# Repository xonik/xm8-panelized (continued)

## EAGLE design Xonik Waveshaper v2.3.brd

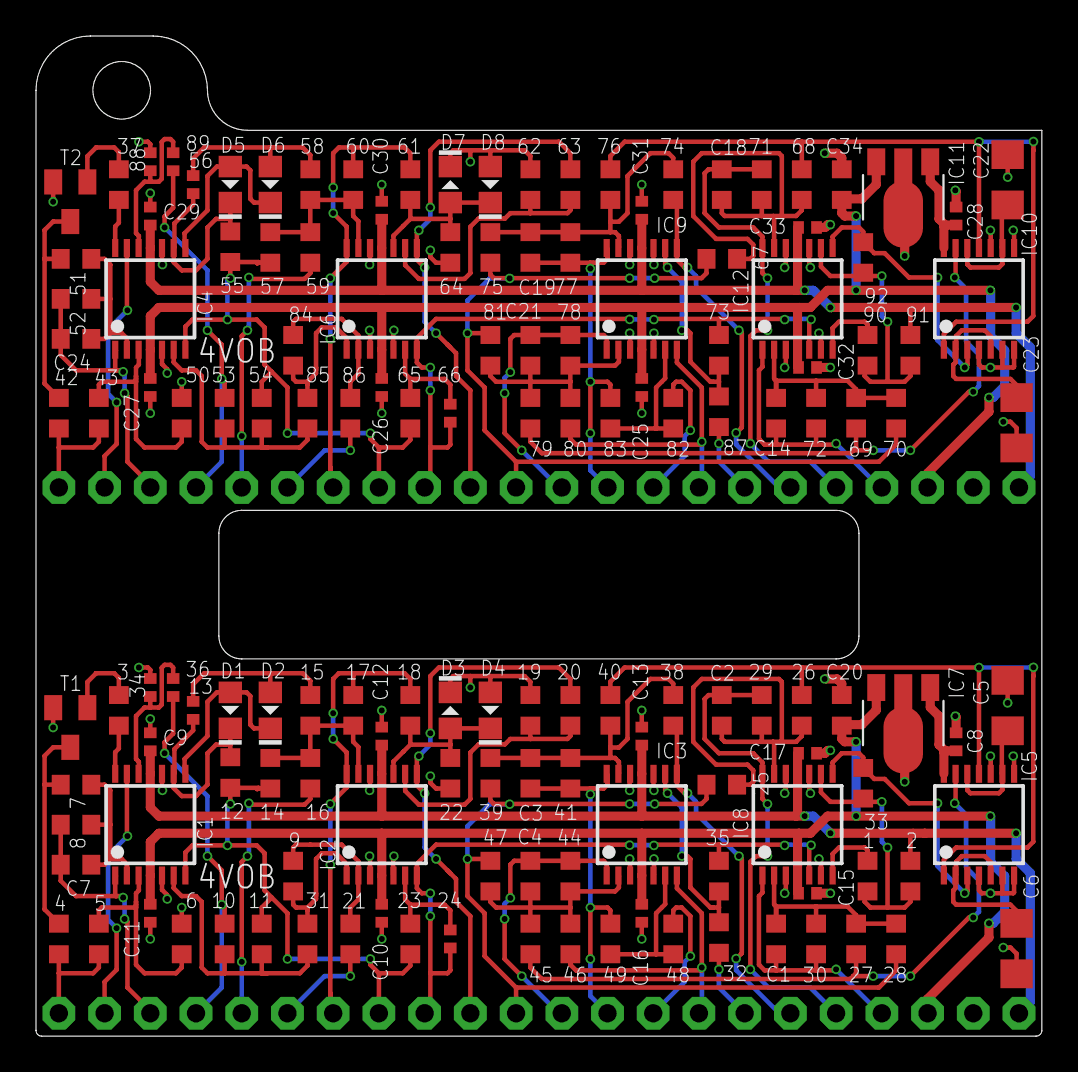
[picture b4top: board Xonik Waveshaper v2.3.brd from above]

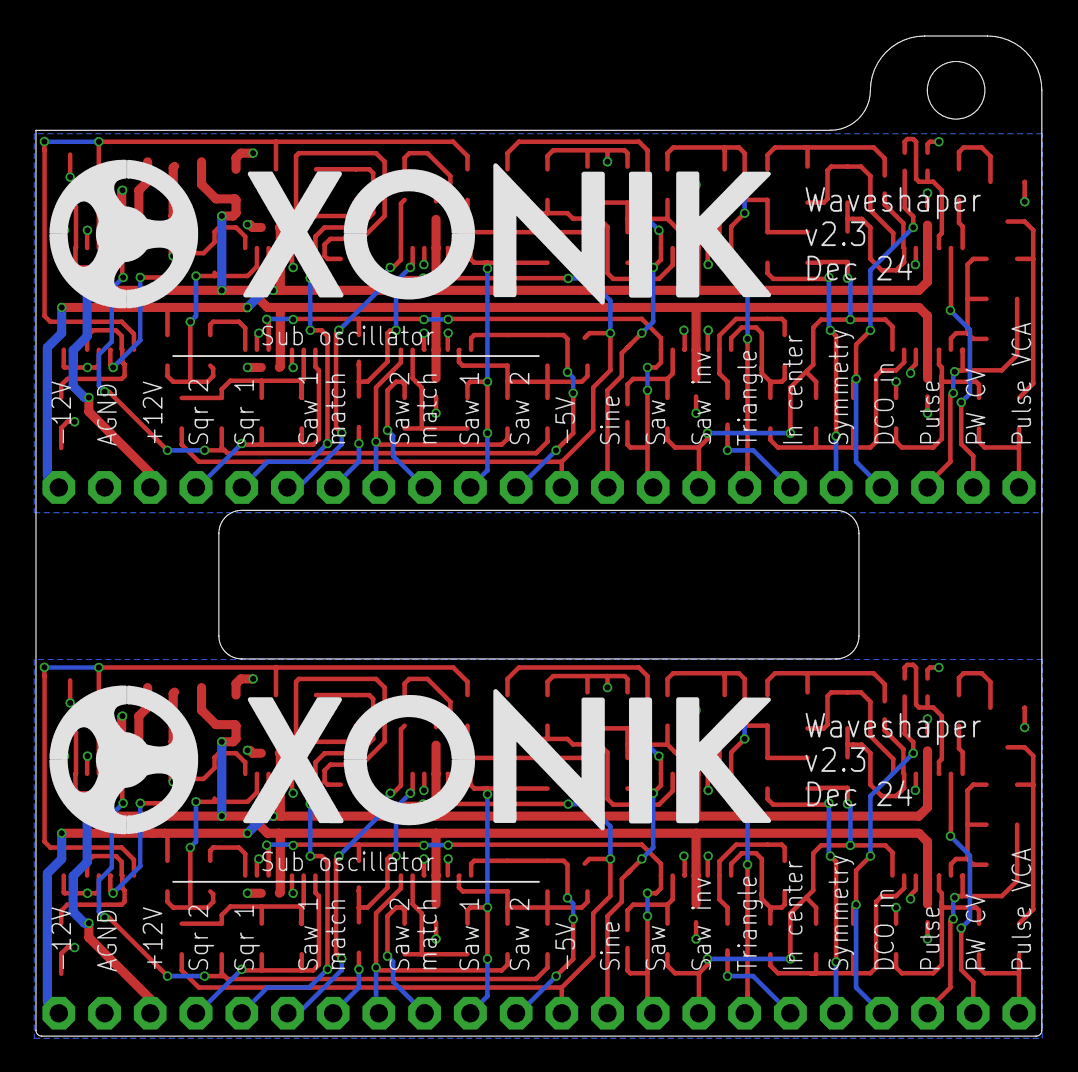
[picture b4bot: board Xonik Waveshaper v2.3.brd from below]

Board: 2 copper layers, 55.9 x 55.6 mm, 152 parts (2 on the bottom side), 104 nets.

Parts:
1, 2, 6, 7, 12, 14, 16, 23, 35, 39, 47, 49, 50, 51, 55, 57, 59, 65, 73, 75, 81, 83, 90, 91: 100k; R0603
3, 37: 68k; R0603
4, 42: 1k; R0603
5, 8, 17, 43, 52, 60: 200k; R0603
9, 84: 30k; R0603
10, 11, 31, 53, 54, 85: 27k; R0603
13, 24, 34, 36, 56, 66, 88, 89: 100k; R0402
15, 40, 45, 58, 76, 79: 50k; R0603
18, 61: 150k; R0603
19, 62: 1k2; R0603
20, 21, 63, 86: 15k; R0603
22, 64: 22k; R0603
25, 28, 29, 30, 33, 67, 70, 71, 72, 92: 20k; R0603
26, 27, 68, 69: 10k; R0603
32, 48, 82, 87: 33k; R0603
38, 41, 44, 46, 74, 77, 78, 80: 49.9k; R0603
C1, C2, C14, C18: 10pF; C0603-J
C3, C4, C19, C21: 30pF; C0603-J
C5, C6, C22, C23: 100nF; C1206
C7, C24: 3pF; C0603-J
C8, C9, C10, C11, C12, C13, C15, C16, C17, C25, C26, C27, C28, C29, C30, C31, C32, C33: 1uF; C0402-J
C20, C34: 0.33uF; C0603-J
D1, D2, D3, D4, D5, D6, D7, D8: 1N41480805; D0805-J
IC1, IC2, IC3, IC4, IC6, IC8, IC9, IC12: TL074JT; TSSOP14J
IC5, IC10: 4013T; TSSOP14J
IC7, IC11: 78L05F; SOT89
T1, T2: 2n3904; SOT23-BEC
U$1, U$2: XONIK_LOGO_40
X1, X2: MA22N-1J

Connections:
+5V: C8.2, IC5.14, IC7.1
+5V1: C28.2, IC10.14, IC11.1
+12V: C10.2, C11.2, C15.2, C16.2, C20.2, IC1.4, IC2.4, IC3.4, IC7.3, IC8.4, X1.20
+12V1: C25.2, C26.2, C27.2, C32.2, C34.2, IC4.4, IC6.4, IC9.4, IC11.3, IC12.4, X2.20
-5V: 25.1, 28.1, 39.2, 47.2, X1.11
-5V1: 67.1, 70.1, 75.2, 81.2, X2.11
-12V: 2.1, C9.1, C12.1, C13.1, C17.1, IC1.11, IC2.11, IC3.11, IC8.11, X1.22
-12V1: 91.1, C29.1, C30.1, C31.1, C33.1, IC4.11, IC6.11, IC9.11, IC12.11, X2.22
AMP_CV: 4.2, 5.2, X1.1
AMP_CV1: 42.2, 43.2, X2.1
DCO_IN: 10.1, 36.1, X1.4
DCO_IN1: 53.1, 89.1, X2.4
GND: 6.2, 19.2, 22.2, 34.2, C5.1, C6.1, C8.1, C9.2, C10.1, C11.1, C12.2, C13.2, C15.1, C16.1, C17.2, C20.1, D3.C, D4.A, IC1.5, IC1.10, IC2.3, IC2.5, IC2.12, IC3.3, IC3.5, IC3.10, IC3.12, IC5.4, IC5.6, IC5.7, IC5.8, IC5.10, IC7.2, IC7.2@1, IC8.3, IC8.6, IC8.10, IC8.12, T1.E, X1.21
GND1: 50.2, 62.2, 64.2, 88.2, C22.1, C23.1, C25.1, C26.1, C27.1, C28.1, C29.2, C30.2, C31.2, C32.1, C33.2, C34.1, D7.C, D8.A, IC4.5, IC4.10, IC6.3, IC6.5, IC6.12, IC9.3, IC9.5, IC9.10, IC9.12, IC10.4, IC10.6, IC10.7, IC10.8, IC10.10, IC11.2, IC11.2@1, IC12.3, IC12.6, IC12.10, IC12.12, T2.E, X2.21
INV_SAW: 11.2, 12.1, 14.1, 23.1, IC1.7, X1.8
INV_SAW1: 54.2, 55.1, 57.1, 65.1, IC4.7, X2.8
IN_CENTER: 21.1, X1.6
IN_CENTER1: 86.1, X2.6
unnamed: 9.1, 21.2, IC2.2
unnamed: 3.2, IC1.14
unnamed: 3.1, T1.B
unnamed: 4.1, 7.1, T1.C
unnamed: 5.1, 6.1, IC1.3
unnamed: 7.2, 8.1, C7.1, IC1.2
unnamed: 1.1, IC8.7
unnamed: 34.1, 36.2, IC1.12
unnamed: 1.2, 2.2, 33.1, IC8.9
unnamed: 10.2, 11.1, 31.2, IC1.6
unnamed: 12.2, 13.1, D1.C, IC1.9
unnamed: D1.A, D2.C, IC1.8
unnamed: 13.2, 15.2, D2.A
unnamed: 14.2, 15.1, 16.1, 17.2, IC2.13
unnamed: 23.2, 24.1, IC2.6
unnamed: 37.2, IC4.14
unnamed: 33.2, IC5.3, IC8.8
unnamed: 37.1, T2.B
unnamed: 25.2, 26.2, 29.1, C2.1, IC8.13
unnamed: 42.1, 51.1, T2.C
unnamed: 48.2, 49.2, IC3.6
unnamed: 27.2, 28.2, 30.1, C1.1, IC8.2
unnamed: 43.1, 50.1, IC4.3
unnamed: 32.1, 35.2, IC3.9
unnamed: 51.2, 52.1, C24.1, IC4.2
unnamed: 38.1, 39.1, 40.2, 41.1, C3.1, IC3.13
unnamed: 53.2, 54.1, 85.2, IC4.6
unnamed: 55.2, 56.1, D5.C, IC4.9
unnamed: 44.1, 45.1, 46.1, 47.1, C4.1, IC3.2
unnamed: D5.A, D6.C, IC4.8
unnamed: C6.2, IC5.2, IC5.5
unnamed: 26.1, 40.1, IC5.1, IC5.11
unnamed: 56.2, 58.2, D6.A
unnamed: C5.2, IC5.9, IC5.12
unnamed: 27.1, 45.2, IC5.13
unnamed: 19.1, 20.2, IC2.9
unnamed: 57.2, 58.1, 59.1, 60.2, IC6.13
unnamed: 65.2, 66.1, IC6.6
unnamed: 18.1, 22.1, D3.A, D4.C, IC2.10
unnamed: 67.2, 68.2, 71.1, C18.1, IC12.13
unnamed: 69.2, 70.2, 72.1, C14.1, IC12.2
unnamed: 9.2, 31.1, IC2.1
unnamed: 73.2, 87.1, IC9.9
unnamed: 74.1, 75.1, 76.2, 77.1, C19.1, IC9.13
unnamed: 82.2, 83.2, IC9.6
unnamed: 78.1, 79.1, 80.1, 81.1, C21.1, IC9.2
unnamed: C23.2, IC10.2, IC10.5
unnamed: 68.1, 76.1, IC10.1, IC10.11
unnamed: C22.2, IC10.9, IC10.12
unnamed: 69.1, 79.2, IC10.13
unnamed: 61.1, 64.1, D7.A, D8.C, IC6.10
unnamed: 62.1, 63.2, IC6.9
unnamed: 84.1, 86.2, IC6.2
unnamed: 84.2, 85.1, IC6.1
unnamed: 88.1, 89.2, IC4.12
unnamed: 90.2, 91.2, 92.1, IC12.9
unnamed: 92.2, IC10.3, IC12.8
unnamed: 90.1, IC12.7
PULSE: 8.2, C7.2, IC1.1, X1.3
PULSE1: 52.2, C24.2, IC4.1, X2.3
PW_CV: IC1.13, X1.2
PW_CV1: IC4.13, X2.2
SAW: 24.2, 35.1, IC2.7, IC8.5, X1.9
SAW1: 66.2, 73.1, IC6.7, IC12.5, X2.9
SINE: 20.1, IC2.8, X1.10
SINE1: 63.1, IC6.8, X2.10
SS1_TRIM_L: 32.2, X1.16
SS1_TRIM_L1: 87.2, X2.16
SS1_TRIM_R: 38.2, IC3.8, X1.17
SS1_TRIM_R1: 74.2, IC9.8, X2.17
SS2_TRIM_L: 48.1, X1.14
SS2_TRIM_L1: 82.1, X2.14
SS2_TRIM_R: 46.2, IC3.7, X1.15
SS2_TRIM_R1: 80.2, IC9.7, X2.15
SUB_SAW_1: 41.2, 49.1, C3.2, IC3.14, X1.13
SUB_SAW_2: 44.2, C4.2, IC3.1, X1.12
SUB_SAW_3: 77.2, 83.1, C19.2, IC9.14, X2.13
SUB_SAW_4: 78.2, C21.2, IC9.1, X2.12
SUB_SQR_1: 29.2, C2.2, IC8.14, X1.18
SUB_SQR_2: 30.2, C1.2, IC8.1, X1.19
SUB_SQR_3: 71.2, C18.2, IC12.14, X2.18
SUB_SQR_4: 72.2, C14.2, IC12.1, X2.19
SYMMETRY: 16.2, X1.5
SYMMETRY1: 59.2, X2.5
TRIANGLE: 17.1, 18.2, IC2.14, X1.7
TRIANGLE1: 60.1, 61.2, IC6.14, X2.7

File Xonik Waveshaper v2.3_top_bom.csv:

Comment,Designator,Footprint,LCSC Part #
MA22N-1J,X1 X2,MA22N-1J,
0.33uF,C20 C34,C0603-J,
1N41480805,D1 D2 D3 D4 D5 D6 D7 D8,D0805-J,
1k,4 42,R0603,
1k2,19 62,R0603,
1uF,C8 C9 C10 C11 C12 C13 C15 C16 C17 C25 C26 C27 C28 C29 C30 C31 C32 C33,C0402-J,
2n3904,T1 T2,SOT23-BEC,
3pF,C7 C24,C0603-J,
10k,26 27 68 69,R0603,
10pF,C1 C2 C14 C18,C0603-J,
15k,20 21 63 86,R0603,
20k,25 28 29 30 33 67 70 71 72 92,R0603,
22k,22 64,R0603,
27k,10 11 31 53 54 85,R0603,
30k,9 84,R0603,
30pF,C3 C4 C19 C21,C0603-J,
33k,32 48 82 87,R0603,
49.9k,38 41 44 46 74 77 78 80,R0603,
50k,15 40 45 58 76 79,R0603,
68k,3 37,R0603,
78L05F,IC7 IC11,SOT89,
100k,1 2 6 7 12,R0603,
100k,13,R0402,
100k,14 16 23,R0603,
100k,24 34,R0402,
100k,35,R0603,
100k,36,R0402,
100k,39 47 49 50 51 55,R0603,
100k,56,R0402,
100k,57 59 65,R0603,
100k,66,R0402,
100k,73 75 81 83,R0603,
100k,88 89,R0402,
100k,90 91,R0603,
100nF,C5 C6 C22 C23,C1206,
150k,18 61,R0603,
200k,5 8 17 43 52 60,R0603,
4013T,IC5 IC10,TSSOP14J,
TL074JT,IC1 IC2 IC3 IC4 IC6 IC8 IC9 IC12,TSSOP14J,

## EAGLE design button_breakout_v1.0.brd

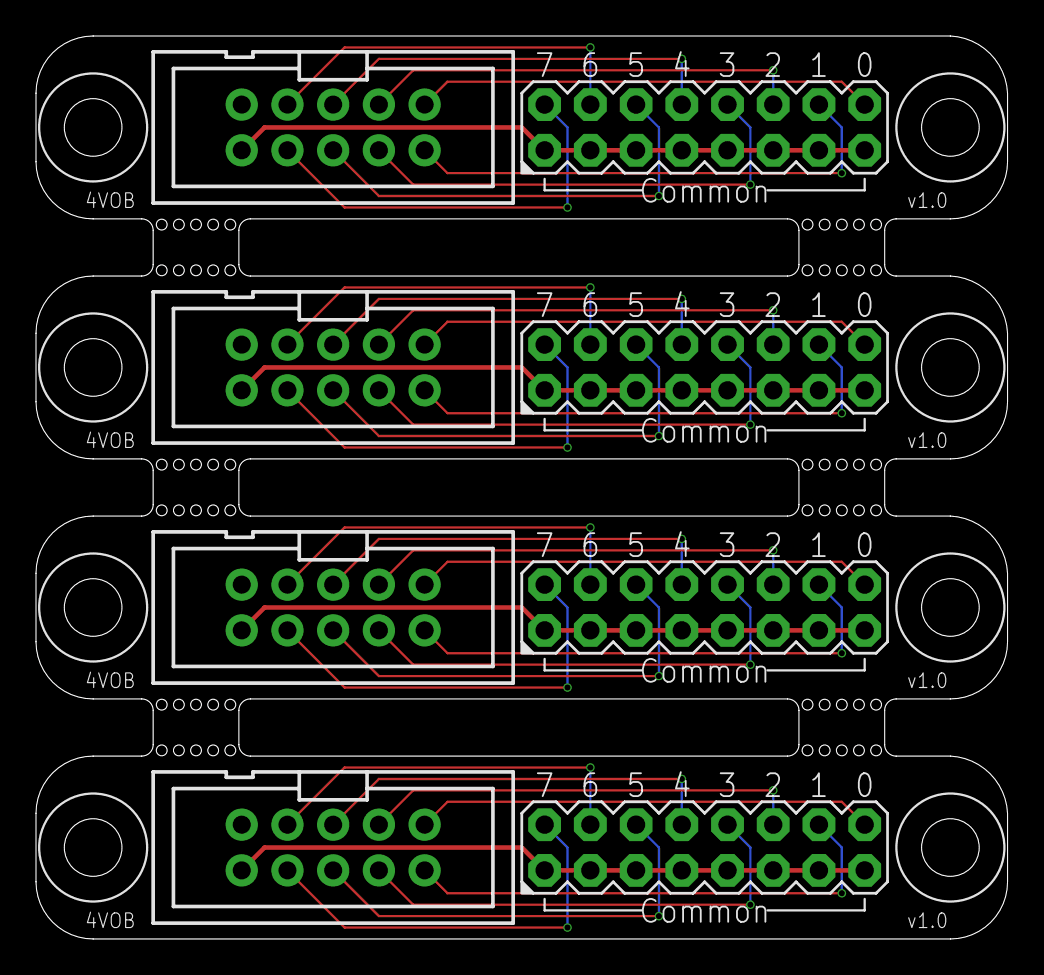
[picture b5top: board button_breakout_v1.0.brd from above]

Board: 2 copper layers, 54.0 x 50.2 mm, 8 parts (0 on the bottom side), 36 nets.

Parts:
IDC, IDC1, IDC2, IDC3: CONN-IDC-10PS; CONN-IDC10P-S
X1, X2, X3, X4: MA08-2J

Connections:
COL0: IDC.1, X1.16
COL1: IDC.2, X1.14
COL2: IDC.3, X1.12
COL3: IDC.4, X1.10
COL4: IDC.5, X1.8
COL5: IDC.6, X1.6
COL6: IDC1.2, X2.14
COL7: IDC.8, X1.2
COL8: IDC1.3, X2.12
COL9: IDC1.4, X2.10
COL10: IDC1.5, X2.8
COL11: IDC1.6, X2.6
COL12: IDC1.8, X2.2
COL13: IDC1.1, X2.16
COL14: IDC1.7, X2.4
COL15: IDC2.2, X3.14
COL16: IDC.7, X1.4
COL17: IDC2.3, X3.12
COL18: IDC2.4, X3.10
COL19: IDC2.5, X3.8
COL20: IDC2.6, X3.6
COL21: IDC2.8, X3.2
COL22: IDC2.1, X3.16
COL23: IDC2.7, X3.4
COL24: IDC3.2, X4.14
COL25: IDC3.3, X4.12
COL26: IDC3.4, X4.10
COL27: IDC3.5, X4.8
COL28: IDC3.6, X4.6
COL29: IDC3.8, X4.2
COL30: IDC3.1, X4.16
COL31: IDC3.7, X4.4
ROW0: IDC.10, X1.1, X1.3, X1.5, X1.7, X1.9, X1.11, X1.13, X1.15
ROW1: IDC1.10, X2.1, X2.3, X2.5, X2.7, X2.9, X2.11, X2.13, X2.15
ROW2: IDC2.10, X3.1, X3.3, X3.5, X3.7, X3.9, X3.11, X3.13, X3.15
ROW3: IDC3.10, X4.1, X4.3, X4.5, X4.7, X4.9, X4.11, X4.13, X4.15

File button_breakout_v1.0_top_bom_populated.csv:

Comment,Designator,Footprint,LCSC Part #
MA08-2J,X1 X2 X3 X4,MA08-2J,C5383108
CONN-IDC-10PS,IDC IDC1 IDC2 IDC3,CONN-IDC10P-S,C429962

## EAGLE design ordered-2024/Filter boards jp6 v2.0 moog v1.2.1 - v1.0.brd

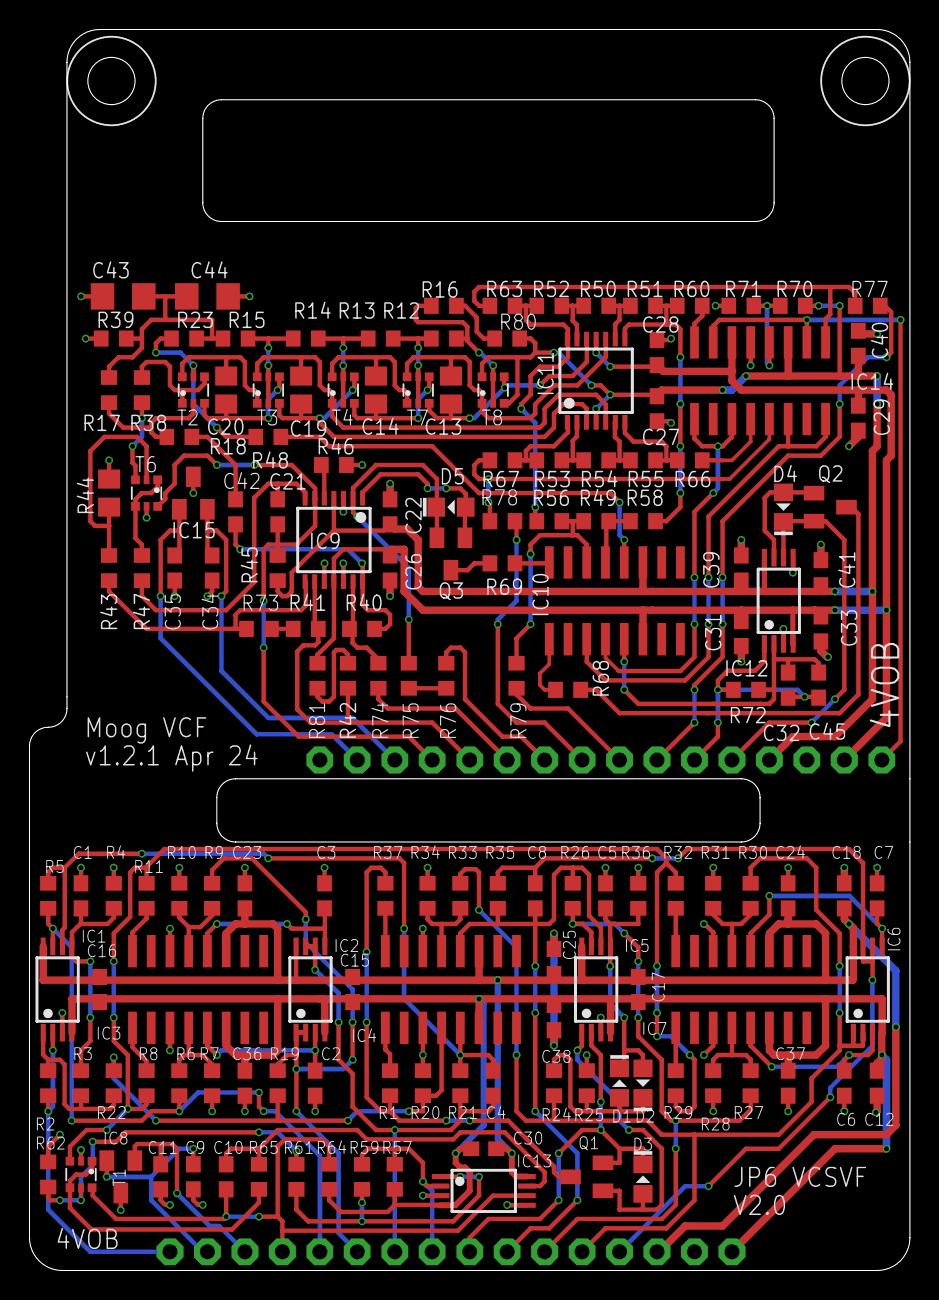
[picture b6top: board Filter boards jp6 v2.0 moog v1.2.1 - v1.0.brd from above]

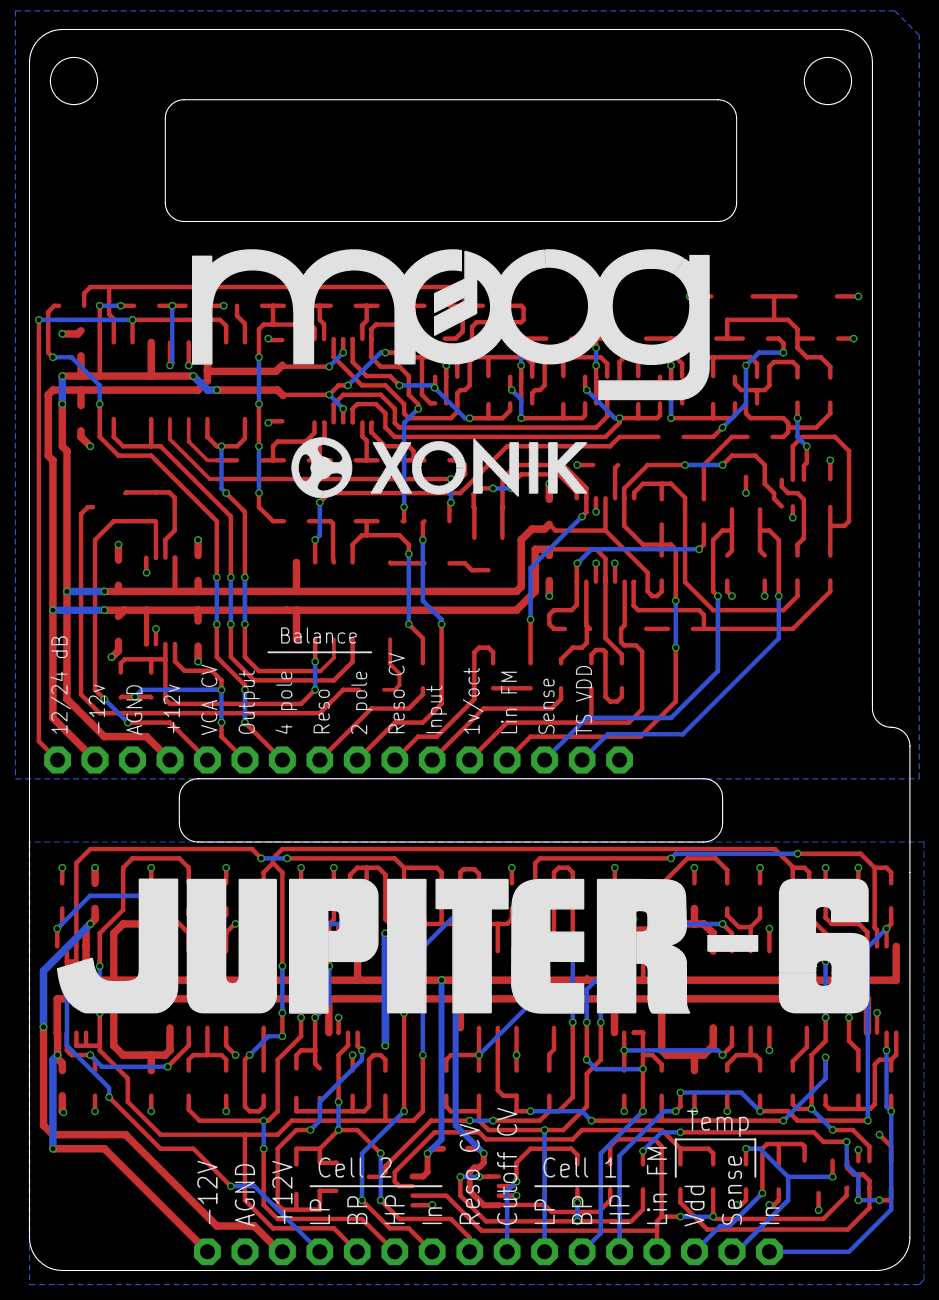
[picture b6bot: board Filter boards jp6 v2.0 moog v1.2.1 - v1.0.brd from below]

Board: 2 copper layers, 59.7 x 84.1 mm, 161 parts (3 on the bottom side), 114 nets.

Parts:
C1, C5, C32, C45: 33p; C0603
C2, C3, C6, C7: 330p; C0603
C4, C8: 5p; C0603
C9, C11, C12, C15, C16, C17, C18, C22, C23, C24, C25, C26, C27, C28, C29, C30, C31, C33, C34, C35, C36, C37, C38, C39, C40, C41, C42: 1uF; C0603
C10: 47p; C0603
C13, C14, C19, C20: 22n; C0805
C21: 100p; C0603
C43, C44: 100uF/6.3V; C1206
D1, D2, D3, D4, D5: 1N41480805; D0805-J
IC1, IC2, IC5, IC6, IC12, IC13: TL072JT; TSSOP8J
IC3, IC4, IC7, IC10: LM13700SL; SO16-NARROW-J
IC8, IC15: MCP9700TT; SOT23J
IC9, IC11: TL074JT; TSSOP14J
IC14: DG403C-JSL; SO16-NARROW-J
Q1, Q2, Q3: MMBT3906LT1SMD; SOT23-BEC
R1, R25, R37, R40, R47, R51, R52, R53, R55, R68, R69: 10k; R0603
R2, R22, R36: 33k; R0603
R3, R24: 47k; R0603
R4, R8, R11, R29, R32: 8k2; R0603
R5, R21, R26, R35, R41, R59, R74: 100k; R0603
R6, R9, R19, R27, R30, R33: 68k; R0603
R7, R10, R20, R28, R31, R34, R62: 560R; R0603
R12, R13, R14, R15, R17, R23, R38, R39, R48: 1k; R0603
R16, R73: 5k6; R0603
R18, R42: 120k; R0603
R43: 56k; R0603
R44: 1k; R0805
R45: 820k; R0603
R46: 1M; R0603
R49: 51R; R0603
R50, R54: 5k1; R0603
R56, R58: 200R; R0603
R57: 330k; R0603
R60, R63, R66, R67: 100R; R0603
R61, R81: 15k; R0603
R64: 1M2; R0603
R65: 1k5; R0603
R70: 105k; R0603
R71: 75k; R0603
R72: 30k; R0603
R75: 3k3; R0603
R76: 18k; R0603
R77, R78: 3k9; R0603
R79: 22k; R0603
R80: 330R; R0603
T1: BC857BS; SOT363J
T2, T3, T4, T6, T7, T8: BC847BS; SOT363J
U$2: JP6_55
U$3, U$6: MA16-1JN; MA16N-1J
U$4: MOOG_35
U$5: XONIK_LOGO_20

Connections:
2P+: IC14.5, R67.1, R78.1
2P-: IC14.4, R66.1
4P+: IC14.9, R63.1, R77.1
4P-: IC14.16, R60.1
12DB_BAL: R78.2, U$6.8
24DB_BAL: R77.2, U$6.10
+12V: C15.1, C16.1, C17.1, C18.1, C23.1, C24.1, C25.1, C30.1, IC1.8, IC2.8, IC3.11, IC4.11, IC5.8, IC6.8, IC7.11, IC13.8, U$3.14
+12V1: C22.2, C27.2, C39.2, C40.2, C41.2, IC9.4, IC10.11, IC11.4, IC12.8, IC14.11, R45.2, R70.1, R80.2, T8.3, T8.6, U$6.13
-12V: C12.2, C15.2, C16.2, C17.2, C30.2, C36.2, C37.2, C38.2, IC1.4, IC2.4, IC3.6, IC4.6, IC5.4, IC6.4, IC7.6, IC13.4, R57.2, R64.2, U$3.16
-12V1: C26.1, C28.1, C29.1, C31.1, C33.1, IC9.11, IC10.6, IC11.11, IC12.4, IC14.14, R81.2, U$6.15
AUDIO: R74.2, U$6.6
AUDIO_SUM: IC9.13, R40.2, R74.1
BP1: IC2.1, IC2.2, R9.1, R19.1, U$3.6
BP2: IC6.1, IC6.2, R24.1, R30.1, R33.1, U$3.12
CUTOFF_CV: IC13.2, R57.1, R59.2, U$3.8
CUTOFF_CV1: IC9.9, R41.2, R42.1, U$6.5
CUTOFF_IABC: R8.2, R11.1, R29.2, R32.1, T1.3
CUTOFF_LIN_FM: C10.1, IC13.6, R64.1, T1.6, U$3.4
GND: C1.2, C2.2, C3.2, C5.2, C6.2, C7.2, C9.1, C11.1, C12.1, C18.2, C23.2, C24.2, C25.2, C36.1, C37.1, C38.1, IC1.3, IC3.3, IC3.14, IC4.3, IC4.14, IC5.3, IC7.3, IC7.14, IC8.3, IC13.3, IC13.5, R4.1, R7.2, R10.1, R20.2, R25.1, R28.2, R31.1, R34.2, R36.1, R62.2, T1.2, U$3.15
GND1: C22.1, C26.2, C27.1, C28.2, C29.2, C31.2, C33.2, C34.1, C35.1, C39.1, C40.1, C41.1, C43.2, C44.2, IC9.3, IC9.10, IC9.12, IC12.3, IC12.5, IC14.13, IC15.3, R39.1, R44.2, R46.2, R71.2, T6.5, U$6.14
HP1: IC1.7, R5.2, R6.2, U$3.5
HP2: IC5.7, R26.2, R27.2, U$3.11
IN1: IC1.2, R2.1, U$3.1
IN2: C8.2, IC4.12, IC5.6, R26.1, R35.2, U$3.10
LIN_FM: C21.1, IC9.6, R45.1, T6.6, U$6.4
LP1: C4.1, IC2.6, IC2.7, R21.1, U$3.7
LP2: C8.1, IC6.6, IC6.7, R35.1, U$3.13
unnamed: C14.1, T4.6, T7.1
unnamed: IC3.1, R8.1
unnamed: IC3.16, R11.2
unnamed: IC4.1, R1.2
unnamed: C19.1, IC11.5, T3.6, T4.1
unnamed: C1.1, IC1.5, R3.2, R4.2
unnamed: C4.2, IC1.6, IC4.5, R5.1, R21.2
unnamed: D3.A, IC5.1, Q1.B
unnamed: IC3.4, R6.1, R7.1
unnamed: IC7.1, R29.1
unnamed: C20.1, T2.6, T3.1
unnamed: C2.1, IC2.3, IC3.5
unnamed: IC7.16, R32.2
unnamed: IC3.13, R9.2, R10.2
unnamed: C3.1, IC2.5, IC3.12
unnamed: C19.2, IC11.3, T3.3, T4.4
unnamed: D1.A, D2.C, R24.2, R25.2
unnamed: C20.2, T2.3, T3.4
unnamed: C14.2, T4.3, T7.4
unnamed: C13.2, IC11.12, T7.3, T8.4
unnamed: IC7.4, R27.1, R28.1
unnamed: C13.1, IC11.10, T7.6, T8.1
unnamed: C6.1, IC6.3, IC7.5
unnamed: IC7.13, R30.2, R31.2
unnamed: C7.1, IC6.5, IC7.12
unnamed: R14.1, R15.2, T3.2, T3.5
unnamed: IC4.13, R33.2, R34.1
unnamed: IC4.16, R37.2
unnamed: C5.1, D1.C, D2.A, IC5.5, R36.2
unnamed: R12.1, R13.2, T7.2, T7.5
unnamed: R17.2, R18.1, T2.2
unnamed: C43.1, C44.1, R15.1, R17.1, R23.1, R39.2
unnamed: R23.2, R48.2, T2.5
unnamed: R38.1, T6.3
unnamed: C42.1, R18.2
unnamed: IC4.4, R19.2, R20.1, R22.2
unnamed: C42.2, IC9.14, R40.1
unnamed: IC9.8, R43.1, R73.1
unnamed: R43.2, R44.1, T6.2
unnamed: IC13.1, R59.1, R61.2
unnamed: C21.2, IC9.7, R47.2
unnamed: R61.1, R62.1, T1.5
unnamed: C10.2, IC13.7, R65.2
unnamed: IC9.5, R46.1
unnamed: R65.1, T1.1, T1.4
unnamed: R47.1, T6.1, T6.4
unnamed: IC10.12, R48.1
unnamed: IC10.13, R49.2, R58.2
unnamed: IC11.13, R50.1, R52.2
unnamed: IC11.14, R52.1, R56.1, R63.2
unnamed: IC11.9, R50.2, R51.2
unnamed: IC11.8, R51.1, R58.1, R60.2
unnamed: IC11.2, R53.2, R54.1
unnamed: IC11.1, R53.1, R67.2
unnamed: IC11.6, R54.2, R55.2
unnamed: IC11.7, R55.1, R66.2
unnamed: C32.1, C45.1, IC10.5, IC12.2, R72.1
unnamed: D4.A, IC12.7, Q2.B
unnamed: Q2.C, R68.1
unnamed: D5.A, IC9.1, Q3.B
unnamed: Q3.C, R69.1
unnamed: R13.1, R14.2, T4.2, T4.5
unnamed: R38.2, T2.1, T2.4
unnamed: R12.2, R16.1, T8.2, T8.5
unnamed: IC14.12, R70.2, R71.1
unnamed: R41.1, R73.2
unnamed: R75.1, R76.2
unnamed: R16.2, R80.1
unnamed: R42.2, R81.1
OUTPUT: C32.2, C45.2, IC12.1, R72.2, U$6.11
POLES_SWITCH: IC14.10, IC14.15, U$6.16
RESO_BAL: R79.1, U$6.9
RESO_BAL_SPLIT: IC10.14, R49.1, R56.2, R79.2
RESO_CV: D3.C, IC5.2, Q1.E, U$3.9
RESO_CV1: R76.1, U$6.7
RESO_CV_MIX: D5.C, IC9.2, Q3.E, R75.2
RESO_IABC: Q1.C, R1.1, R37.1
RESO_I_ABC: IC10.16, R69.2
SVF1_IN: IC1.1, R2.2, R3.1, R22.1
TEMP_SENSE: C9.2, IC8.2, U$3.2
TEMP_SENSE1: C34.2, IC15.2, U$6.3
TS_VDD: C11.2, IC8.1, U$3.3
TS_VDD1: C35.2, IC15.1, U$6.2
VCA_CV: D4.C, IC12.6, Q2.E, U$6.12
VCA_I_ABC: IC10.1, R68.2
VCA_NEG: IC10.4, IC14.1, IC14.3
VCA_POS: IC10.3, IC14.6, IC14.8

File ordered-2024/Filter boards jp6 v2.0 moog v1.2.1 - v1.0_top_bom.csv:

Comment,Designator,Footprint,LCSC Part #
1M,R46,R0603,
1M2,R64,R0603,
1N41480805,D1 D2 D3 D4 D5,D0805-J,
1k,R12 R13 R14 R15 R17 R23 R38 R39,R0603,
1k,R44,R0805,
1k,R48,R0603,
1k5,R65,R0603,
1uF,C9 C11 C12 C15 C16 C17 C18 C22 C23 C24 C25 C26 C27 C28 C29 C30 C31 C33 C34 C35 C36 C37 C38 C39 C40 C41 C42,C0603,
3k3,R75,R0603,
3k9,R77 R78,R0603,
5k1,R50 R54,R0603,
5k6,R16 R73,R0603,
5p,C4 C8,C0603,
8k2,R4 R8 R11 R29 R32,R0603,
10k,R1 R25 R37 R40 R47 R51 R52 R53 R55 R68 R69,R0603,
15k,R61 R81,R0603,
18k,R76,R0603,
22k,R79,R0603,
22n,C13 C14 C19 C20,C0805,
30k,R72,R0603,
33k,R2 R22 R36,R0603,
33p,C1 C5 C32 C45,C0603,
47k,R3 R24,R0603,
47p,C10,C0603,
51R,R49,R0603,
56k,R43,R0603,
68k,R6 R9 R19 R27 R30 R33,R0603,
75k,R71,R0603,
100R,R60 R63 R66 R67,R0603,
100k,R5 R21 R26 R35 R41 R59 R74,R0603,
100p,C21,C0603,
100uF/6.3V,C43 C44,C1206,
105k,R70,R0603,
120k,R18 R42,R0603,
200R,R56 R58,R0603,
330R,R80,R0603,
330k,R57,R0603,
330p,C2 C3 C6 C7,C0603,
560R,R7 R10 R20 R28 R31 R34 R62,R0603,
820k,R45,R0603,
BC847BS,T2 T3 T4 T6 T7 T8,SOT363J,
BC857BS,T1,SOT363J,
DG403C-JSL,IC14,SO16-NARROW-J,
LM13700SL,IC3 IC4 IC7 IC10,SO16-NARROW-J,
MA16-1JN,U$3 U$6,MA16N-1J,
MCP9700TT,IC8 IC15,SOT23J,
MMBT3906LT1SMD,Q1 Q2 Q3,SOT23-BEC,
TL072JT,IC1 IC2 IC5 IC6 IC12 IC13,TSSOP8J,
TL074JT,IC9 IC11,TSSOP14J,

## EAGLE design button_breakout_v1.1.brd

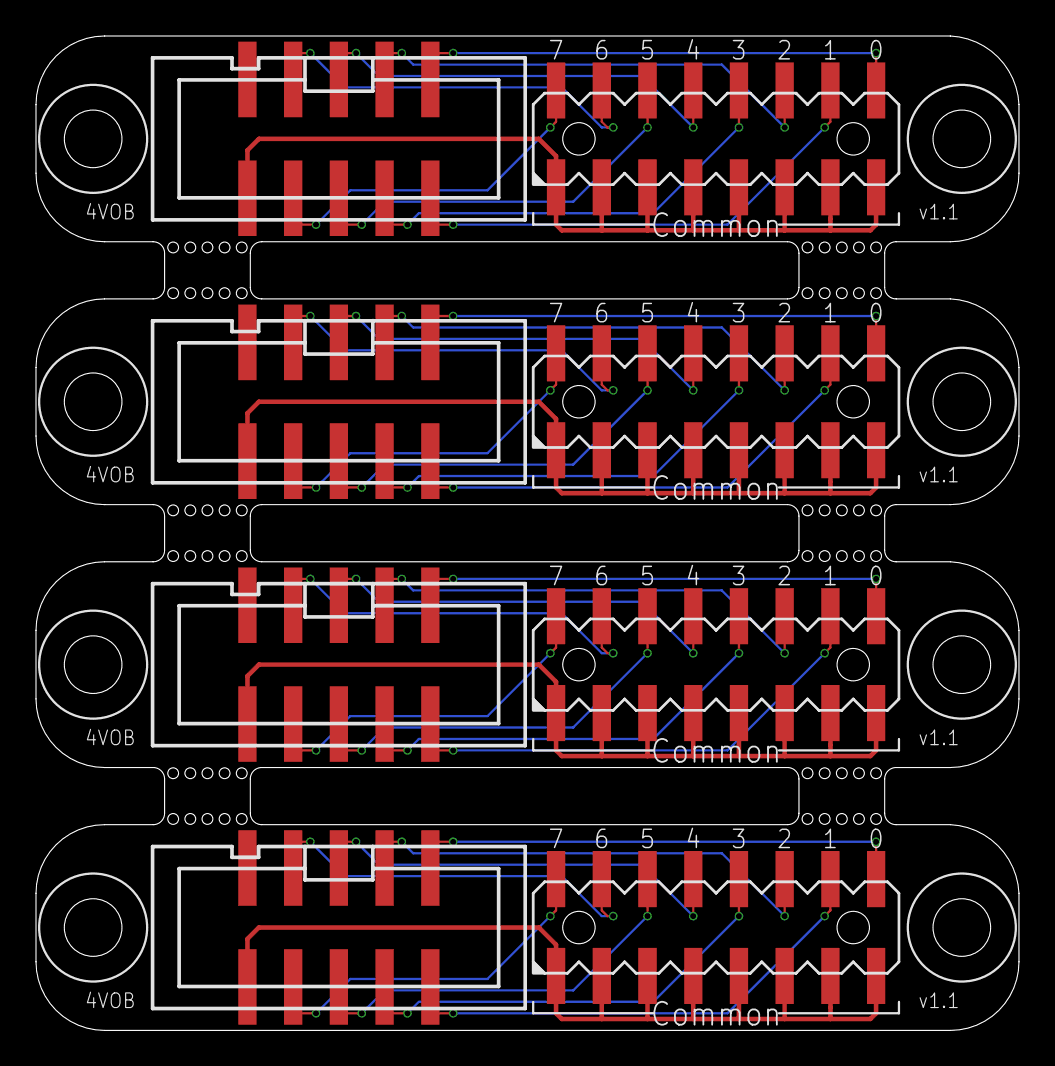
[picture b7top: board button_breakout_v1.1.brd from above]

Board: 2 copper layers, 54.6 x 55.2 mm, 8 parts (0 on the bottom side), 36 nets.

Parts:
IDC, IDC1, IDC2, IDC3: CONN-IDC-10PSMD; CONN-IDC10P-SMD
X1, X2, X3, X4: MA08-2-SMDJ

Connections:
COL0: IDC.P$1, X1.P$16
COL1: IDC.P$2, X1.P$14
COL2: IDC.P$3, X1.P$12
COL3: IDC.P$4, X1.P$10
COL4: IDC.P$5, X1.P$8
COL5: IDC.P$6, X1.P$6
COL6: IDC.P$7, X1.P$4
COL7: IDC.P$8, X1.P$2
COL8: IDC1.P$2, X2.P$14
COL9: IDC1.P$3, X2.P$12
COL10: IDC1.P$4, X2.P$10
COL11: IDC1.P$5, X2.P$8
COL12: IDC1.P$6, X2.P$6
COL13: IDC1.P$7, X2.P$4
COL14: IDC1.P$8, X2.P$2
COL15: IDC1.P$1, X2.P$16
COL16: IDC2.P$2, X3.P$14
COL17: IDC2.P$3, X3.P$12
COL18: IDC2.P$4, X3.P$10
COL19: IDC2.P$5, X3.P$8
COL20: IDC2.P$6, X3.P$6
COL21: IDC2.P$7, X3.P$4
COL22: IDC2.P$8, X3.P$2
COL23: IDC2.P$1, X3.P$16
COL24: IDC3.P$2, X4.P$14
COL25: IDC3.P$3, X4.P$12
COL26: IDC3.P$4, X4.P$10
COL27: IDC3.P$5, X4.P$8
COL28: IDC3.P$6, X4.P$6
COL29: IDC3.P$7, X4.P$4
COL30: IDC3.P$8, X4.P$2
COL31: IDC3.P$1, X4.P$16
ROW0: IDC.P$10, X1.P$1, X1.P$3, X1.P$5, X1.P$7, X1.P$9, X1.P$11, X1.P$13, X1.P$15
ROW1: IDC1.P$10, X2.P$1, X2.P$3, X2.P$5, X2.P$7, X2.P$9, X2.P$11, X2.P$13, X2.P$15
ROW2: IDC2.P$10, X3.P$1, X3.P$3, X3.P$5, X3.P$7, X3.P$9, X3.P$11, X3.P$13, X3.P$15
ROW3: IDC3.P$10, X4.P$1, X4.P$3, X4.P$5, X4.P$7, X4.P$9, X4.P$11, X4.P$13, X4.P$15

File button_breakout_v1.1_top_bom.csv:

Comment,Designator,Footprint,LCSC Part #
MA08-2-SMDJ,X1 X2 X3 X4,MA08-2-SMDJ,
CONN-IDC-10PSMD,IDC IDC1 IDC2 IDC3,CONN-IDC10P-SMD,

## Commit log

2025-02-26 Added panelized boards for the first time
2025-03-01 Moved and changed order
2025-03-01 Added Bus mixer
2025-03-01 Order completed
